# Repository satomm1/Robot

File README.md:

# Mobile Robot
This repository contains many instructions for setting up and constructing the robot. However, for a comprehensive guide, please visit: [https://satomm1.github.io/mattbot/instructions.html](https://satomm1.github.io/mattbot/index.html).

## Authors
Matthew Sato and Kincho Law<br>
satomm@stanford.edu<br>
Stanford University Department of Civil and Environmental Engineering<br>
Engineering Informatics Lab

## Description
This repo contains mechanical (CAD) designs, electrical schematics, and software for creating a wheeled mobile robot.

- The mechanical design is provided in the `./CAD` directory. In this directory, you will find [detailed instructions](./CAD/README.md) for constructing the mobile robot along with relevant STL/DXF files and a bill of materials. The CAD files were generated in Inventor.
- The electrical design for the various components are located in the `./Electrical` directory. In this directory, you will find electrical schematics and the PCB design for the main control board, IMU breakout board, microphone breakout board, and microphone controller board. A [detailed list of the components and instructions](./Electrical/README.md) for each of these boards is included.
- The software design for the main control board is in the `./Software` directory. This software is for the PIC32 located on the main control board and facilitates communication between the PIC32 and Jetson, performs PID control, odometry, etc. Additionally, the software for the microphone control board is included in this directory. Please visit the [README](./Software/README.md) for more detailed instructions.
- Instructions for the Nvidia Jetson Orin Nano aare provided in the `./Jetson` directory. This directory includes instructions for bringing up the Jetson, setting up the WiFi mesh node connectivity, setting up the Docker environments, and setting up the ROS environment/software stack. Please visit the [Jetson README](./Jetson/README.md) for more details.

## License

This project is licensed under the MIT License - see the [LICENSE](LICENSE) file for details.

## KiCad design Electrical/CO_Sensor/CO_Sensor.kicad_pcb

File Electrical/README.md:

# Electrical

Contains the electrical schematics and PCB gerber files for the Robot electronics. There are several Schematics/PCB designs for a variety of uses:
- Main Board - the main motor controller and communicator with the Jetson
- Microphone - a breakout board for a Mems omnidirectional microphone
- IMU Breakout - a breakout board containing a 6-axis IMU
- Reflective Sensor - a breakout board containing a sensor for very short distance measurements

The Main Board is the only required electronics, so start here. The others (IMU, reflective, microphone) provide additional functionality should you wish to include them.

## Ordering a Manufactured PCB Board
You can use a variety of vendors to order a PCB. I have used JLPCB in the past. To order, all you need to do is submit the zipped `gerber_files` folder to the vendor.

## Main Board
The [main board](./MainBoard/) contains the PIC32 MCU, motor drivers, power supply, button sensors, Jetson communications, etc. In this directory, you will find a comprehensive schematic and PCB layout, as well as ready to use Gerber files for PCB manufacturing.

After populating the board, we need to make several connections from the board to other components of the mobile robot:

1. Connecting to the motors

    - The motors should be connected to the motor terminals via a 6 position female molex connector. Insert the wires corresponding to the markings on the PCB silkscreen.

2. Connecting to the Jetson

    - The jetson is connected via a 6 position female molex connector on the PCB, and dupont connectors on the Jetson header. Only the first five positions on the PCB need to be connected (SCK, SS, SDO, SDI, GND) and must be matched to the corresponding SPI pins on the Jetson header. For example, if using SPI1 (SPI3) on the jetson:

        | Jetson Pin Name       | Jetson GPIO | PCB Pin Name |
        |-----------------------|-------------|--------------|
        | SPI1_SCLK (SPI3_SCLK) | 23 (13)     | SCK          |
        | SPI1_CS0 (SPI3_CS0)   | 24 (18)     | SS           |
        | SPI1_din (SPI3_din)   | 21 (22)     | SDO          |
        | SPI1_dout (SPI3_dout) | 19 (37)     | SDI          |
        | GND                   | 25 (20)     | GND          |

    - **Note:** If using twisted pair wire, **DO NOT** twist the SDO and SDI wires together. This will lead to unintended crosstalk that can significantly degrade the ability of the Jetson to communicate with the PCB.

3. Connecting to the power supply
    
    - Insert the Tamiya style leads for the NiMH batteries into the tall power blocks. The positive (red) and negative (black) terminals are indicated on the PCB via +/- silkscreen. 
    - Connect to the main power switch. The rocker switch should be connected to the 4 position Molex terminal near the battery terminals. Solder four wires to the rocker switch (with heat shrink tubing to protect the connection) and connect the other four ends to the corresponding female molex connector. The positions are as follows:

    - Insert a 5A fuse into the fuse holder.
    - Insert the micro-usb cable for the 5V battery into the port at the front of the board (the other micro-usb port is used for serial debugging)
    - Now, you can power on the PCB with the rocker switch. Alternatively, the small switch on the PCB is used to provide only 5V power supply access to the board in case you do not need to run the motors.

4. Connecting to the buttons
    
    - Solder a pair of wires to each button (with heat shrink tubing to protect the cunnection) and connect the other ends of the wire to a 2-position female molex connector.

## Microphone

For detailed instructions on the Microphone, visit the [Microphone README Page](./Microphones/README.md).

## IMU Breakout
For detailed instructions on the IMU, visit the [IMU README Page](./IMU_Breakout/README.md).

## Reflective Sensor

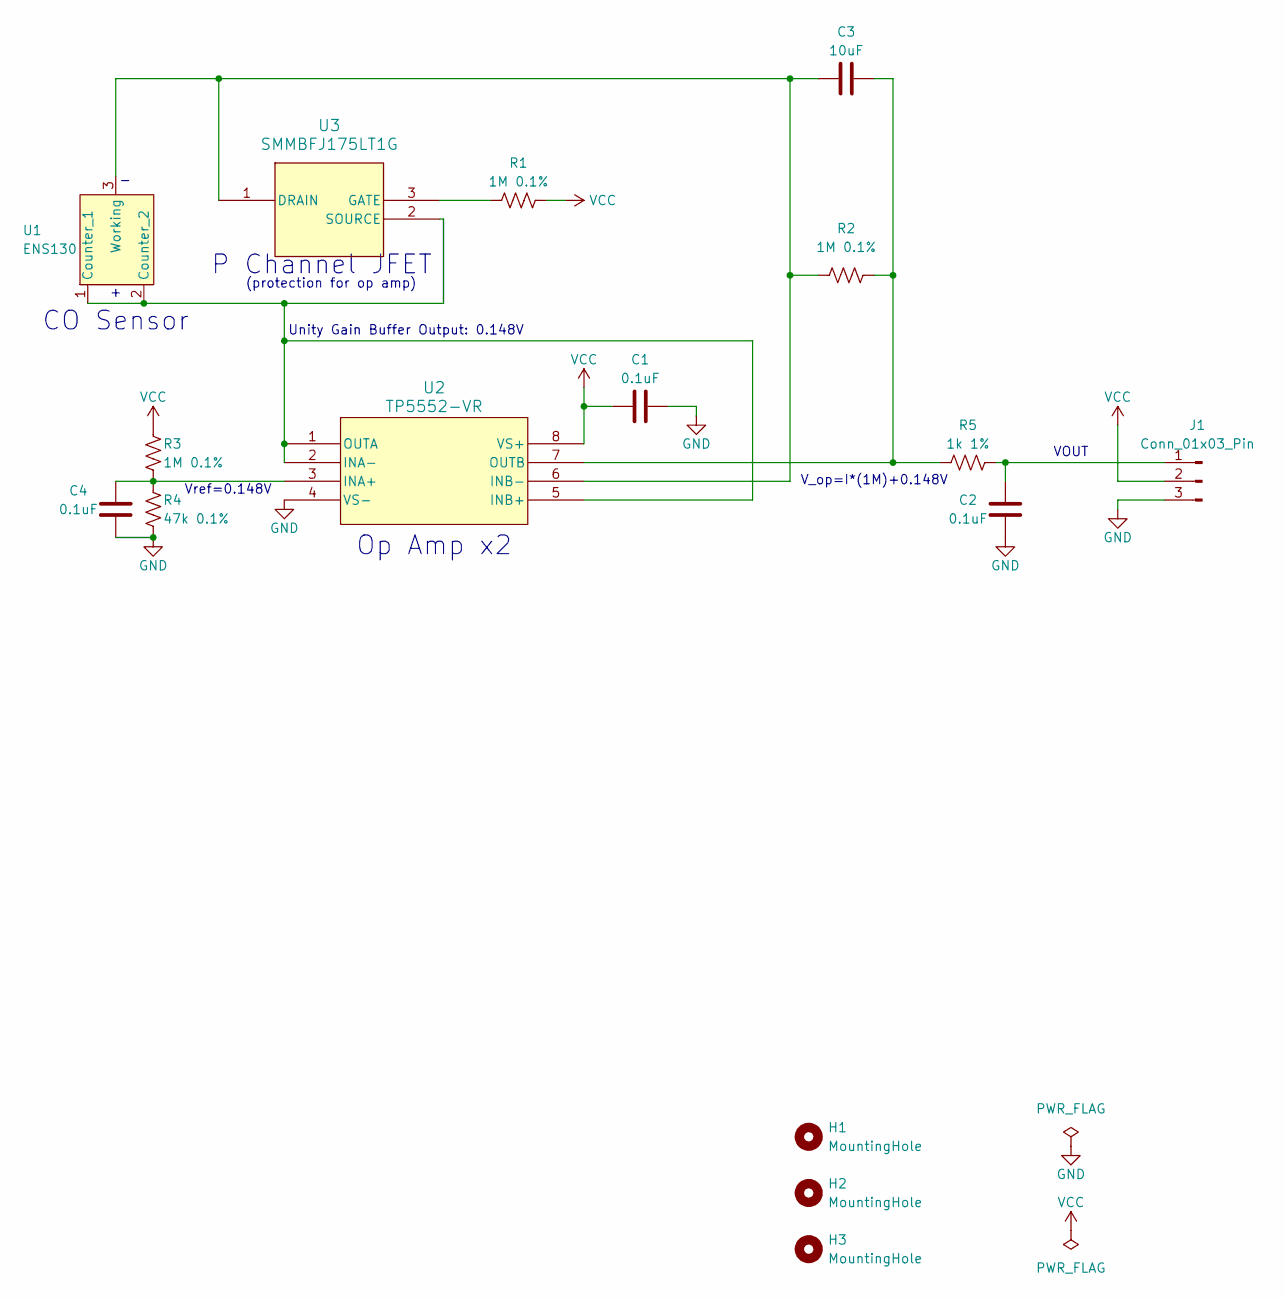
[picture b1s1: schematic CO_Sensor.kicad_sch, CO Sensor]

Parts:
C1, C2, C4: 0.1uF; C_0805_2012Metric_Pad1.18x1.45mm_HandSolder; Mfr P/N CL21B104KBCNNNC
C3: 10uF; C_0805_2012Metric_Pad1.18x1.45mm_HandSolder; Mfr P/N CL21A106KOQNNNE
H1, H2, H3: MountingHole; MountingHole_3.2mm_M3
J1: Conn_01x03_Pin; PinHeader_1x03_P2.54mm_Vertical
R1, R2, R3: 1M 0.1%; R_0805_2012Metric_Pad1.20x1.40mm_HandSolder; Mfr P/N ERA-6AEB105V
R4: 47k 0.1%; R_0805_2012Metric_Pad1.20x1.40mm_HandSolder; Mfr P/N ERA-6AEB473V
R5: 1k 1%; R_0805_2012Metric_Pad1.20x1.40mm_HandSolder; Mfr P/N RMCF0805FT1K00
U1: ENS130; Mfr P/N ENS130
U2: TP5552-VR; VS1MSOP-8-A_TPK-M; Mfr P/N TP5552-VR
U3: SMMBFJ175LT1G; SOT-23_ONS-M; Mfr P/N SMMBFJ175LT1G

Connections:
GND: C1.2, C2.1, C4.1, J1.3, R4.1, U2.4 (VS-)
unnamed: C2.2, J1.1, R5.1
unnamed: U1.1 (Counter_1), U1.2 (Counter_2), U2.1 (OUTA), U2.2 (INA-), U2.5 (INB+), U3.2 (SOURCE)
unnamed: C3.1, R2.1, U1.3 (Working), U2.6 (INB-), U3.1 (DRAIN)
unnamed: C4.2, R3.1, R4.2, U2.3 (INA+)
unnamed: C3.2, R2.2, R5.2, U2.7 (OUTB)
unnamed: R1.1, U3.3 (GATE)
VCC: C1.1, J1.2, R1.2, R3.2, U2.8 (VS+)

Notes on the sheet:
Unity Gain Buffer Output: 0.148V
CO Sensor
P Channel JFET
Op Amp x2
Vref=0.148V
(protection for op amp)
VOUT
V_op=I*(1M)+0.148V

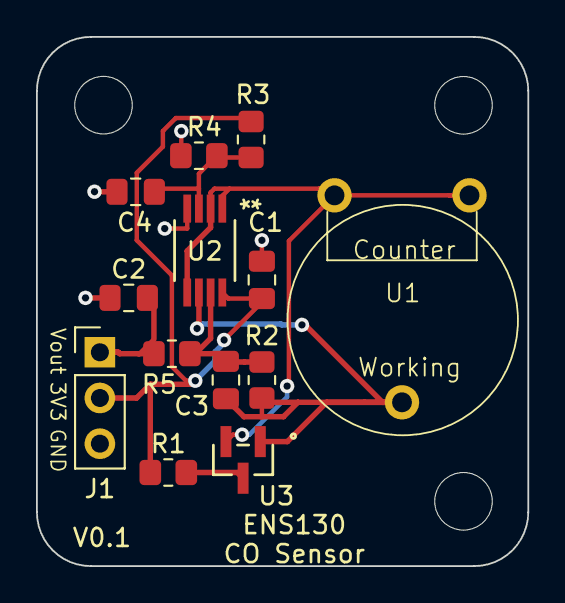
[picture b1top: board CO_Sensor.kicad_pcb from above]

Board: 2 copper layers, 27.3 x 29.4 mm, 16 parts (0 on the bottom side), 8 nets.

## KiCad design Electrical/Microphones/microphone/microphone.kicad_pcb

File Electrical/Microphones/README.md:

# Microphone Design

This directory holds the electrical design for the microphones. Note, you will need one  PIC32 board and two microphone boards for a single system. The two microphones allows for stereo audio. The PIC32 board is an intermediary that translates the audio signal into a format that the Jetson can read.

> [!WARNING] 
> Soldering the microphones is not easy. You will need solder paste and a reflow oven.  You can order a stencil for the solder paste, or manually apply the solder paste to the microphone pads (be careful not to add too much solder!).

> [!TIP]
> Make sure to solder the 6 pin right angle connector in the correct direction. See picture below for guidance.

## Putting the Microphones Together
Once you have a soldered microphone PCB, we can construct the full microphone in its housing. 3D print the housings (instructions in the [Mechanical Directory](../../CAD/README.md)). For a more robust microphone, we use a gasket and an acoustically transparent fabric to prevent debris from entering the microphone port. To construct the housing

1. Attach the gasket, making a hole slightly larger than the microphone port (be sure the hole is big enough even after the gasket is compressed). For the gasket, I use a foam-like double sided tape.

2. Place the acoustically transparent membrane over the gasket and PCB, cut holes for the screws. For the acoustically transparent fabric, I use Muslin (which can be picked up at your local fabric store).

3. Attach the PCB to the 3D printed housing using two screws.

4. Connect the two microphones to the PIC32 Control Board using Molex Connectors.

## Setting up the PIC32
Once you have a soldered PIC32, you must program it with the source code located in the [PIC32 Firmware](./PIC32%20Firmware/) directory. Connect the two microphones to the PIC32 board. Connect the PIC32 board to the Jetson's I2S pins. Then, follow the instructions at https://github.com/satomm1/mattbot_record/tree/noetic for Jetson software.

## PIC32 to Jetson I2S Pin Mapping

We will be using the 6-pin connector for this microphone (ignore the 5 pin header). Make sure the switch is switched in the upward position. Then, connect the pins on the PIC32 Board to the Jetson using the following connections (may need to adjust pin # based on your hardware):

| PIC32 Pin | Jetson I2S Pin | Jetson I2S Pin Number |
|-----------|----------------|-----------------------|
| CS        | I2S2_FS        | 35 |
| SDI       | I2S2_DOUT      | 40 |
| SDO       | I2S2_DIN       | 38 |
| SCK       | I2S2_SCLK      | 12 |
| GND       | GND            | 14 |
| 3V3       | 3.3V           | 17 |

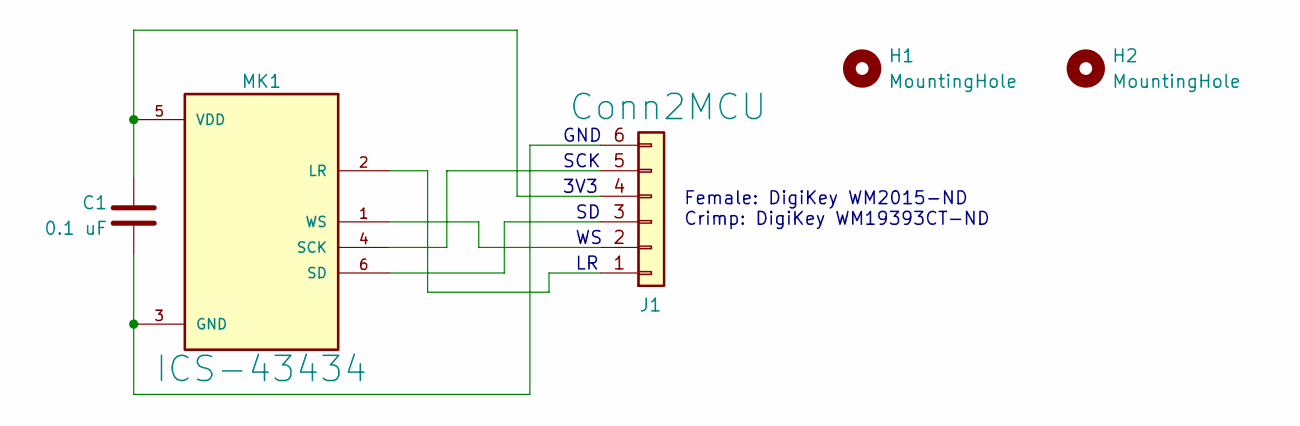
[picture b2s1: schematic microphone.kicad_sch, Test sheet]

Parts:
C1: 0.1 uF; C_0805_2012Metric_Pad1.18x1.45mm_HandSolder; Mfr P/N CL21B104KBCNNNC
H1, H2: MountingHole; MountingHole_3.2mm_M3
J1: Conn2MCU; CONN_22-05-3061_MOL; Mfr P/N 0022053061
MK1: ICS-43434; MIC_ICS-43434; Mfr P/N ICS-43434

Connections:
unnamed: J1.1, MK1.2 (LR)
unnamed: J1.2, MK1.1 (WS)
unnamed: J1.3, MK1.6 (SD)
unnamed: C1.1, J1.4, MK1.5 (VDD)
unnamed: J1.5, MK1.4 (SCK)
unnamed: C1.2, J1.6, MK1.3 (GND)

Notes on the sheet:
GND
Female: DigiKey WM2015-ND Crimp: DigiKey WM19393CT-ND
3V3
SCK

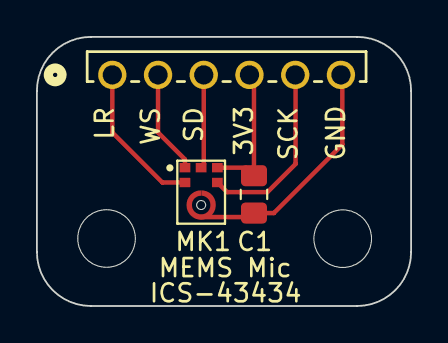
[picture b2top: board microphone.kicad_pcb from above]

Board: 2 copper layers, 20.8 x 15.0 mm, 5 parts (0 on the bottom side), 6 nets.

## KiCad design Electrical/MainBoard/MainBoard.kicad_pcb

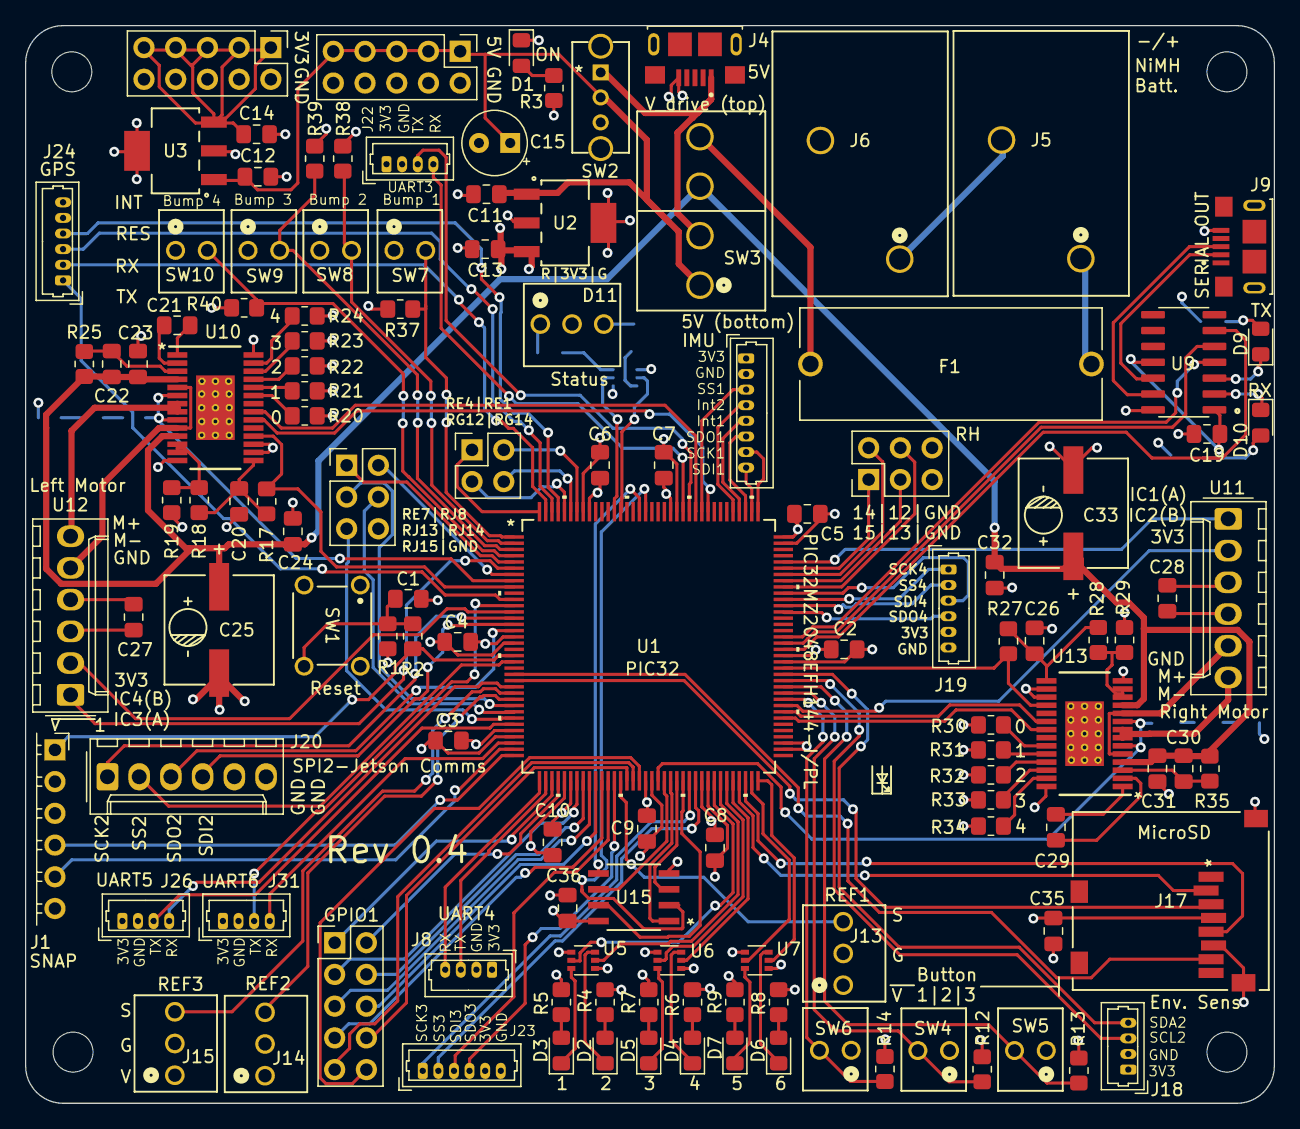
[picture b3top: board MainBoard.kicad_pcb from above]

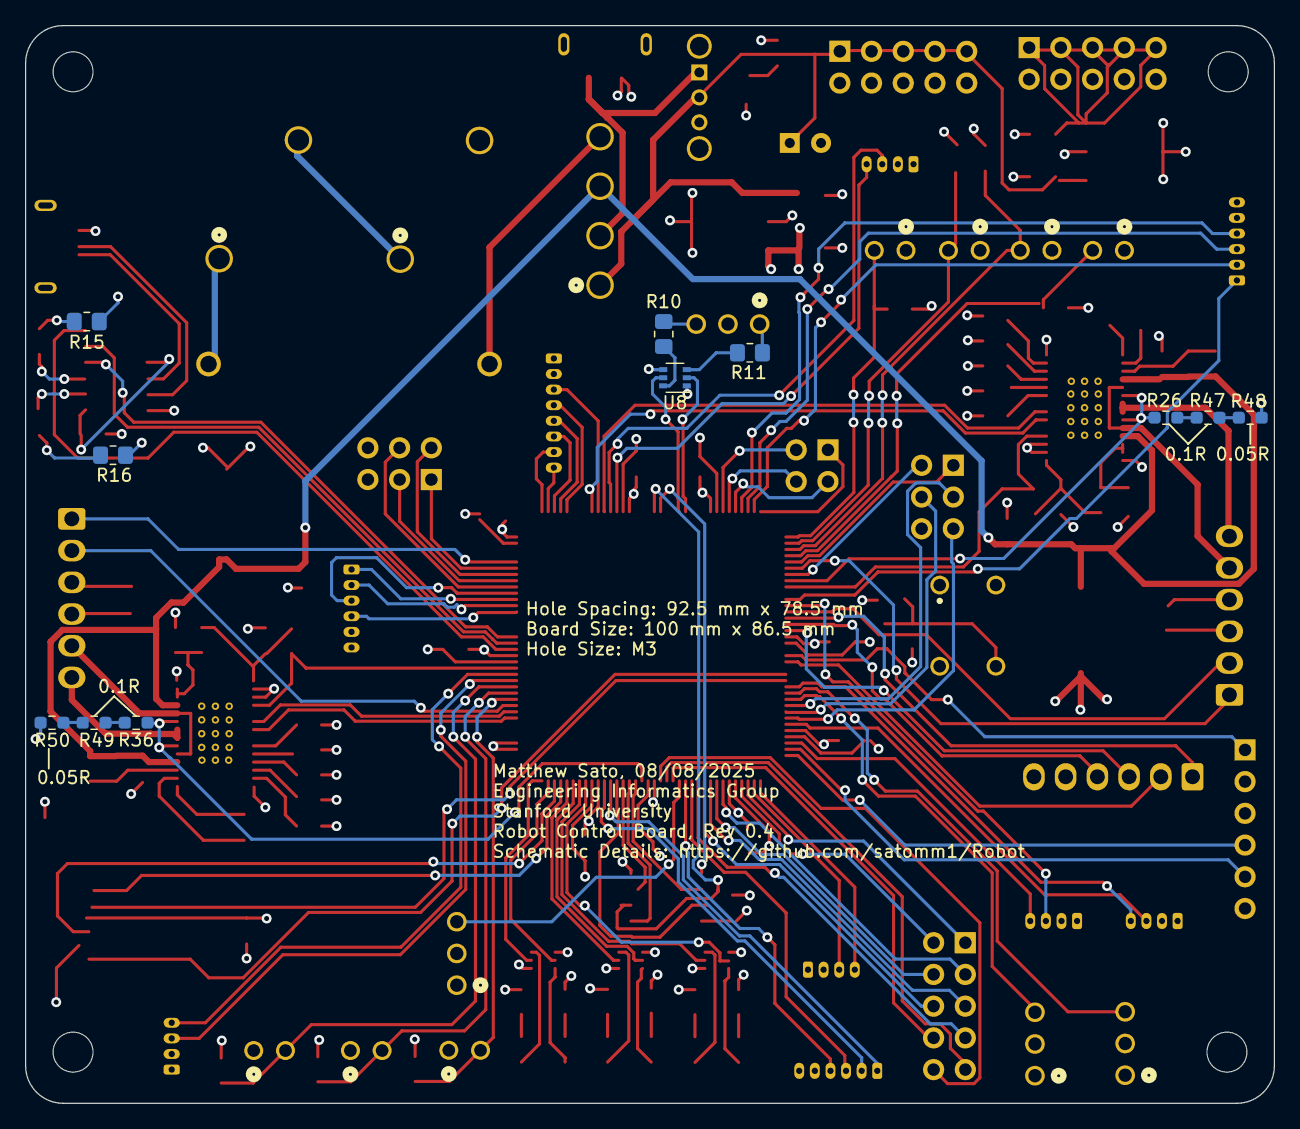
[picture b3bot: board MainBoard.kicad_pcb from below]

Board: 4 copper layers, 100.0 x 86.3 mm, 139 parts (11 on the bottom side), 162 nets.

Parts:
C1, C2, C3, C4, C5, C6, C7, C8, C9, C10, C19, C22, C23, C24, C27, C28, C30, C31, C32, C35, C36: 0.1 uF; C_0805_2012Metric_Pad1.18x1.45mm_HandSolder
C11, C12, C13, C14: 4.7 uF; C_0805_2012Metric_Pad1.18x1.45mm_HandSolder
C15: 10 uF; CP_Radial_Tantal_D5.0mm_P2.50mm
C20, C26: 0.47 uF; C_0805_2012Metric_Pad1.18x1.45mm_HandSolder
C21, C29: 0.01 uF; C_0805_2012Metric_Pad1.18x1.45mm_HandSolder
C25, C33: 100 uF; PCAP_8x10-ELECT_NCA-M
D1, D2, D3, D4, D5, D6, D7, D9, D10: LED; LED_0805_2012Metric_Pad1.15x1.40mm_HandSolder
D11: Status_LED; CONN3_22232031_MOL
F1: 5A Fuse; FUSE_4628
H1, H2, H3, H4: MountingHole; MountingHole_3.2mm_M3
J1: SNAP Program; PinSocket_1x06_P2.54mm_Horizontal
J2: 3.3V Supply; PinHeader_2x05_P2.54mm_Vertical
J3: 5V Supply; PinHeader_2x05_P2.54mm_Vertical
J4, J9: USB_B_Micro; AMPHENOL_10118193-0001LF
J5, J6: Battery1; CONN_1017514
J7: GPIO1; PinHeader_2x05_P2.54mm_Vertical
J8, J18, J22, J26, J31: Conn_01x04; Molex_PicoBlade_53047-0410_1x04_P1.25mm_Vertical
J13, J14, J15: Refl_PCB_Connect; CONN3_22232031_MOL
J16, J21: Conn_02x03_Odd_Even; PinHeader_2x03_P2.54mm_Vertical
J17: MEM2061-01-188-00-A; MEM2061-01-188-00-A_GCT
J19, J23, J24: Conn_01x06; Molex_PicoBlade_53047-0610_1x06_P1.25mm_Vertical
J20: Conn_01x06; Molex_KK-254_AE-6410-06A_1x06_P2.54mm_Vertical
J25: Conn_02x02_Odd_Even; PinHeader_2x02_P2.54mm_Vertical
J30: Conn_01x08; Molex_PicoBlade_53047-0810_1x08_P1.25mm_Vertical
R1, R17, R27: 10k; R_0805_2012Metric_Pad1.20x1.40mm_HandSolder
R2, R12, R13, R14, R37, R38, R39, R40: 1k; R_0805_2012Metric_Pad1.20x1.40mm_HandSolder
R3, R4, R5, R6, R7, R8, R9, R10, R11, R15, R16: 130R; R_0805_2012Metric_Pad1.20x1.40mm_HandSolder
R18, R28: 16k; R_0805_2012Metric_Pad1.20x1.40mm_HandSolder
R19, R29: 51k; R_0805_2012Metric_Pad1.20x1.40mm_HandSolder
R20, R21, R22, R23, R24, R30, R31, R32, R33, R34: 0R; R_0805_2012Metric_Pad1.20x1.40mm_HandSolder
R25, R35: 1M; R_0805_2012Metric_Pad1.20x1.40mm_HandSolder
R26, R36, R47, R49: 0.1R; R_0603_1608Metric_Pad0.98x0.95mm_HandSolder
R48, R50: 0.05 R; R_0603_1608Metric_Pad0.98x0.95mm_HandSolder
SW1: Reset; SW_B3F-1000_OMR
SW2: 5V Bypass; SPDT_OS102011_CNK
SW3: All Power Switch; 26-60-4040_MOL
SW4, SW5, SW6: User_Button; CONN_22232021_MOL
SW7, SW8, SW9, SW10: SW_SPST; CONN_22232021_MOL
U1: PIC32MZ2048EFH144-I/PL; LQFP144_PL_MCH-M
U2, U3: AP2114HA-3.3TRG1; SOT-223_DIO-M
U5, U6, U7, U8: GSF7002DW; SOT-363_SC-70-6
U9: MCP2221A-I_SL; SOIC127P600X175-14N
U10, U13: DRV8842PWPR; PWP0028C_M
U11, U12: Quad_Encoder_Motor; Molex_KK-254_AE-6410-06A_1x06_P2.54mm_Vertical
U15: M95M01-DFMN6TP; SO8N_4X5X1P27_STM-M

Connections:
+3.3V: C2.1, C3.2, C4.2, C5.1, C6.1, C7.2, C8.1, C9.1, C10.2, C13.1, C19.1, C27.1, C28.1, C35.2, C36.2, D11.2 (A), J1.2, J8.1, J13.1, J14.1, J15.1, J17.P4 (VDD), J18.1, J19.5, J22.1, J23.5, J24.5, J26.1, J30.1, J31.1, R1.2, R3.1, R4.1, R5.1, R6.1, R7.1, R8.1, R9.1, R15.1, R16.1, R20.1, R21.1, R22.1, R23.1, R24.1, R30.1, R31.1, R32.1, R33.1, R34.1, SW4.1, SW5.1, SW6.1, SW7.1 (A), SW8.1 (A), SW9.1 (A), SW10.1 (A), U1.18 (VDD), U1.33 (VDD), U1.41 (AVDD), U1.55 (VDD), U1.64 (VDD), U1.88 (VDD), U1.107 (VDD), U1.122 (VDD), U1.137 (VDD), U2.3 (VOUT), U9.1 (VDD), U9.11 (VUSB), U10.16 (RESET_N), U10.17 (SLEEP_N), U11.3 (Vcc), U12.3 (Vcc), U13.16 (RESET_N), U13.17 (SLEEP_N), U15.8 (VCC)
+5V: C11.1, C12.1, C15.1, J3.1, J3.3, J3.5, J3.7, J3.9, SW2.2 (B), SW3.1, U2.1 (VIN), U3.1 (VIN)
/Bump1: R37.1, SW7.2 (B), U1.1 (AN23/RG15)
/Bump2: R38.1, SW8.2 (B), U1.2 (EBIA5/AN34/PMA5/RA5)
/Bump3: R39.1, SW9.2 (B), U1.3 (EBID5/AN17/RPE5/PMD5/RE5)
/Bump4: R40.1, SW10.2 (B), U1.4 (EBID6/AN16/PMD6/RE6)
/Dir1: U1.80 (SCL3/RPF8/RF8), U13.20 (IN2)
/Dir2: U1.117 (EBIA22/RJ3), U10.20 (IN2)
/Fault1: R17.1, U1.9 (EBIBS0/RJ12), U10.18 (FAULT_N)
/Fault2: R27.1, U1.87 (EBIA14/PMCS1/PMA14/RA4), U13.18 (FAULT_N)
/GPS_INT: J24.4, U1.141 (TRD0/SQID0/RG13)
/GPS_Reset: J24.3, U1.142 (EBID2/PMD2/RE2)
/Hold*: U1.60 (AN8/RB13), U15.7 (*HOLD)
/IC1: U1.104 (RPD0/RTCC/INT0/RD0), U11.1 (PhaseA)
/IC2: U1.81 (ERXD0/RH8), U11.2 (PhaseB)
/IC3: U1.6 (EBIA6/AN22/RPC1/PMA6/RC1), U12.1 (PhaseA)
/IC4: U1.13 (EBIOE/AN19/RPC4/PMRD/RC4), U12.2 (PhaseB)
/IMU_INT1: J30.5, U1.112 (EBID12/RPD12/PMD12/RD12)
/IMU_INT2: J30.4, U1.113 (EBID13/PMD13/RD13)
/LED1: U1.66 (AN41/ERXD1/RH5), U5.2 (G1)
/LED2: U1.65 (AN40/ERXERR/RH4), U5.5 (G2)
/LED3: U1.68 (EBIA4/PMA4/RH7), U6.2 (G1)
/LED4: U1.67 (AN42/ERXD2/RH6), U6.5 (G2)
/LED5: U1.72 (OSC2/CLKO/RC15), U7.2 (G1)
/LED6: U1.71 (OSC1/CLKI/RC12), U7.5 (G2)
/MotorCurrent1: R26.2, U1.8 (AN36/ETXD1/RJ9), U10.6 (ISEN), U10.9 (ISEN)
/MotorCurrent2: R36.2, U1.56 (TCK/AN29/RA1), U13.6 (ISEN), U13.9 (ISEN)
/OC1: U1.79 (SDA3/RPF2/RF2), U13.21 (IN1)
/OC2: U1.119 (SQICS1/RPD5/RD5), U10.21 (IN1)
/RA9: J7.1, U1.39 (VREF-/CVREF-/AN27/RA9)
/RA10: J7.2, U1.40 (VREF+/CVREF+/AN28/RA10)
/RB8: J7.7, U1.47 (EBIA10/AN48/RPB8/PMA10/RB8)
/RE1: J25.2, U1.138 (EBID1/PMD1/RE1)
/RE4: J25.1, U1.144 (EBID4/AN18/PMD4/RE4)
/RE7: J16.1, U1.5 (EBID7/AN15/PMD7/RE7)
/RG12: J25.3, U1.140 (TRD1/SQID1/RG12)
/RG14: J25.4, U1.139 (TRD2/SQID2/RG14)
/RH0: J7.3, U1.43 (AN38/ETXD2/RH0)
/RH1: J7.4, U1.44 (AN39/ETXD3/RH1)
/RH2: J7.5, U1.45 (EBIRP/RH2)
/RH3: J7.6, U1.46 (RH3)
/RH12: J21.4, U1.100 (ECRS/RH12)
/RH13: J21.3, U1.101 (ERXDV/ECRSDV/RH13)
/RH14: J21.2, U1.102 (RH14)
/RH15: J21.1, U1.103 (EBIA23/RH15)
/RJ8: J16.2, U1.7 (AN35/ETXD0/RJ8)
/RJ13: J16.3, U1.28 (EBIA13/PMA13/RJ13)
/RJ14: J16.4, U1.29 (EBIA11/PMA11/RJ14)
/RJ15: J16.5, U1.30 (EBIA0/PMA0/RJ15)
/RK1: J7.8, U1.51 (EBIA1/PMA1/RK1)
/RK2: J7.9, U1.52 (EBIA3/PMA3/RK2)
/RK3: J7.10, U1.53 (EBIA17/RK3)
/Refl1: J13.3, U1.50 (AN6/RB11)
/Refl2: J14.3, U1.27 (AN37/ERXCLK/EREFCLK/RJ11)
/Refl3: J15.3, U1.26 (AN4/C1INB/RB4)
/SCK1: J30.7, U1.109 (RPD1/SCK1/RD1)
/SCK2: J20.1, U1.14 (AN14/C1IND/RPG6/SCK2/RG6)
/SCK3: J23.1, U1.61 (AN9/RPB14/SCK3/RB14)
/SCK4: J19.1, U1.98 (RPD10/SCK4/RD10)
/SCK5: U1.57 (TDI/AN30/RPF13/SCK5/RF13), U15.6 (C)
/SCK6: J17.P5 (CLK), U1.70 (AN33/RPD15/SCK6/RD15)
/SCL2: J18.3, U1.85 (SCL2/RA2)
/SDA2: J18.4, U1.86 (EBIRDY1/SDA2/RA3)
/SDI1: J30.8, U1.110 (EBID14/RPD2/PMD14/RD2)
/SDI2: J20.4, U1.15 (AN13/C1INC/RPG7/SDA4/RG7)
/SDI3: J23.3, U1.48 (EBIA7/AN49/RPB9/PMA7/RB9)
/SDI4: J19.3, U1.99 (EMDC/RPD11/RD11)
/SDI5: U1.127 (EBID9/RPG1/PMD9/RG1), U15.2 (Q)
/SDI6: J17.P7 (DAT0), U1.23 (AN25/RPE8/RE8)
/SDO1: J30.6, U1.111 (EBID15/RPD3/PMD15/RD3)
/SDO2: J20.3, U1.16 (AN12/C2IND/RPG8/SCL4/RG8)
/SDO3: J23.4, U1.49 (CVREFOUT/AN5/RPB10/RB10)
/SDO4: J19.4, U1.96 (RPA15/SDA1/RA15)
/SDO5: U1.128 (EBID8/RPG0/PMD8/RG0), U15.5 (D)
/SDO6: J17.P3 (CMD), U1.24 (AN26/RPE9/RE9)
/SS1*: J30.3, U1.118 (SQICS0/RPD4/RD4)
/SS2*: J20.2, U1.21 (EBIA2/AN11/C2INC/RPG9/PMA2/RG9)
/SS3*: J23.2, U1.62 (AN10/RPB15/OCFB/RB15)
/SS4*: J19.2, U1.97 (EBIA15/RPD9/PMCS2/PMA15/RD9)
/SS5*: U1.58 (TDO/AN31/RPF12/RF12), U15.1 (*S)
/SS6*: J17.P2 (CD/DAT3), U1.69 (AN32/RPD14/RD14)
/Status_Green: U1.132 (EBICS1/RJ5), U8.2 (G1)
/Status_Yellow: U1.131 (EBICS0/RJ4), U8.5 (G2)
/Switch1: R14.1, SW6.2, U1.82 (ERXD3/RH9)
/Switch2: R12.1, SW4.2, U1.83 (ECOL/RH10)
/Switch3: R13.1, SW5.2, U1.84 (EBIRDY2/RH11)
/U1RX: U1.90 (EBIA9/RPF4/SDA5/PMA9/RF4), U9.6 (UTX)
/U1TX: U1.91 (EBIA8/RPF5/SCL5/PMA8/RF5), U9.5 (URX)
/U2RX: J24.2, U1.143 (EBID3/RPE3/PMD3/RE3)
/U2TX: J24.1, U1.11 (EBIA12/AN21/RPC2/PMA12/RC2)
/U3RX: J22.4, U1.121 (ETXCLK/RPD7/RD7)
/U3TX: J22.3, U1.120 (ETXEN/RPD6/RD6)
/U4RX: J8.4, U1.37 (PGEC2/AN46/RPB6/RB6)
/U4TX: J8.3, U1.38 (PGED2/AN47/RPB7/RB7)
/U5RX: J26.4, U1.25 (AN45/C1INA/RPB5/RB5)
/U5TX: J26.3, U1.31 (AN3/C2INA/RPB3/RB3)
/U6RX: J31.4, U1.34 (AN2/C2INB/RPB2/RB2)
/U6TX: J31.3, U1.12 (EBIWE/AN20/RPC3/PMWR/RC3)
/USB_RST: U1.92 (EBIA18/RK4), U9.4 (~RST)
/Write Protect*: U1.59 (AN7/RB12), U15.3 (*W)
GND: C1.2, C2.2, C3.1, C4.1, C5.2, C6.2, C7.1, C8.2, C9.2, C10.1, C11.2, C12.2, C13.2, C14.2, C15.2, C19.2, C20.2, C23.2, C24.2, C25.2, C26.2, C27.2, C28.2, C31.2, C32.2, C33.2, C35.1, C36.1, D1.1 (K), J1.3, J2.2, J2.4, J2.6, J2.8, J2.10, J3.2, J3.4, J3.6, J3.8, J3.10, J4.5 (GND), J6.2, J8.2, J9.5 (GND), J13.2, J14.2, J15.2, J16.6, J17.11 (GROUND), J17.12 (GROUND), J17.P6 (VSS), J18.2, J19.6, J20.5, J20.6, J21.5, J21.6, J22.2, J23.6, J24.6, J26.2, J30.2, J31.2, R12.2, R13.2, R14.2, R19.2, R29.2, R37.2, R38.2, R39.2, R40.2, R48.1, R50.1, SW1.1, U1.17 (VSS), U1.32 (VSS), U1.42 (AVSS), U1.54 (VSS), U1.63 (VSS), U1.74 (VUSB3V3), U1.75 (VSS), U1.89 (VSS), U1.108 (VSS), U1.123 (VSS), U1.136 (VSS), U2.2 (GND), U2.4 (GND), U3.2 (GND), U3.4 (GND), U5.1 (S1), U5.4 (S2), U6.1 (S1), U6.4 (S2), U7.1 (S1), U7.4 (S2), U8.1 (S1), U8.4 (S2), U9.14 (VSS), U10.14 (GND), U10.28 (GND), U10.29 (PAD), U11.4 (GND), U12.4 (GND), U13.14 (GND), U13.28 (GND), U13.29 (PAD), U15.4 (VSS)
unnamed: C1.1, R1.1, R2.2, SW1.4
unnamed: D1.2 (A), R3.2
unnamed: D2.2 (A), R4.2
unnamed: D2.1 (K), U5.3 (D2)
unnamed: D3.2 (A), R5.2
unnamed: D3.1 (K), U5.6 (D1)
unnamed: D4.2 (A), R6.2
unnamed: D4.1 (K), U6.3 (D2)
unnamed: D5.2 (A), R7.2
unnamed: D5.1 (K), U6.6 (D1)
unnamed: D6.2 (A), R8.2
unnamed: D6.1 (K), U7.3 (D2)
unnamed: D7.2 (A), R9.2
unnamed: D7.1 (K), U7.6 (D1)
unnamed: D9.2 (A), R15.2
unnamed: D9.1 (K), U9.3 (GP1)
unnamed: D10.2 (A), R16.2
unnamed: D10.1 (K), U9.2 (GP0)
unnamed: D11.1 (K1), R11.2
unnamed: D11.3 (K2), R10.2
unnamed: F1.1, SW3.4
unnamed: J1.1, R2.1, U1.20 (MCLR)
unnamed: J1.4, U1.36 (PGED1/AN0/RPB0/RB0)
unnamed: J1.5, U1.35 (PGEC1/AN1/RPB1/RB1)
unnamed: C14.1, J2.1, J2.3, J2.5, J2.7, J2.9, U3.3 (VOUT)
unnamed: J4.1 (VBUS), SW2.1 (A), SW3.2
unnamed: F1.2, J5.1
unnamed: J5.2, J6.1
unnamed: J9.3 (D+), U9.13 (D+)
unnamed: J9.2 (D-), U9.12 (D-)
unnamed: R18.2, R19.1, U10.12 (VREF), U10.13 (VREF)
unnamed: R26.1, R47.2
unnamed: R28.2, R29.1, U13.12 (VREF), U13.13 (VREF)
unnamed: R36.1, R49.2
unnamed: R47.1, R48.2
unnamed: R49.1, R50.2
unnamed: R10.1, U8.6 (D1)
unnamed: R11.1, U8.3 (D2)
unnamed: C21.1, U10.1 (CP1)
unnamed: C21.2, U10.2 (CP2)
unnamed: R20.2, U10.23 (I0)
unnamed: R21.2, U10.24 (I1)
unnamed: R22.2, U10.25 (I2)
unnamed: R23.2, U10.26 (I3)
unnamed: R24.2, U10.27 (I4)
unnamed: C20.1, R17.2, R18.1, U10.15 (V3P3OUT)
unnamed: C22.2, R25.2, U10.3 (VCP)
unnamed: U11.5 (M+), U13.5 (OUT1), U13.10 (OUT1)
unnamed: U11.6 (M-), U13.7 (OUT2), U13.8 (OUT2)
unnamed: U10.5 (OUT1), U10.10 (OUT1), U12.5 (M+)
unnamed: U10.7 (OUT2), U10.8 (OUT2), U12.6 (M-)
unnamed: C29.1, U13.1 (CP1)
unnamed: C29.2, U13.2 (CP2)
unnamed: R30.2, U13.23 (I0)
unnamed: R31.2, U13.24 (I1)
unnamed: R32.2, U13.25 (I2)
unnamed: R33.2, U13.26 (I3)
unnamed: R34.2, U13.27 (I4)
unnamed: C26.1, R27.2, R28.1, U13.15 (V3P3OUT)
unnamed: C30.1, R35.2, U13.3 (VCP)
Vdrive: C22.1, C23.1, C24.1, C25.1, C30.2, C31.1, C32.1, C33.1, R25.1, R35.1, SW3.3, U10.4 (VM), U10.11 (VM), U13.4 (VM), U13.11 (VM)

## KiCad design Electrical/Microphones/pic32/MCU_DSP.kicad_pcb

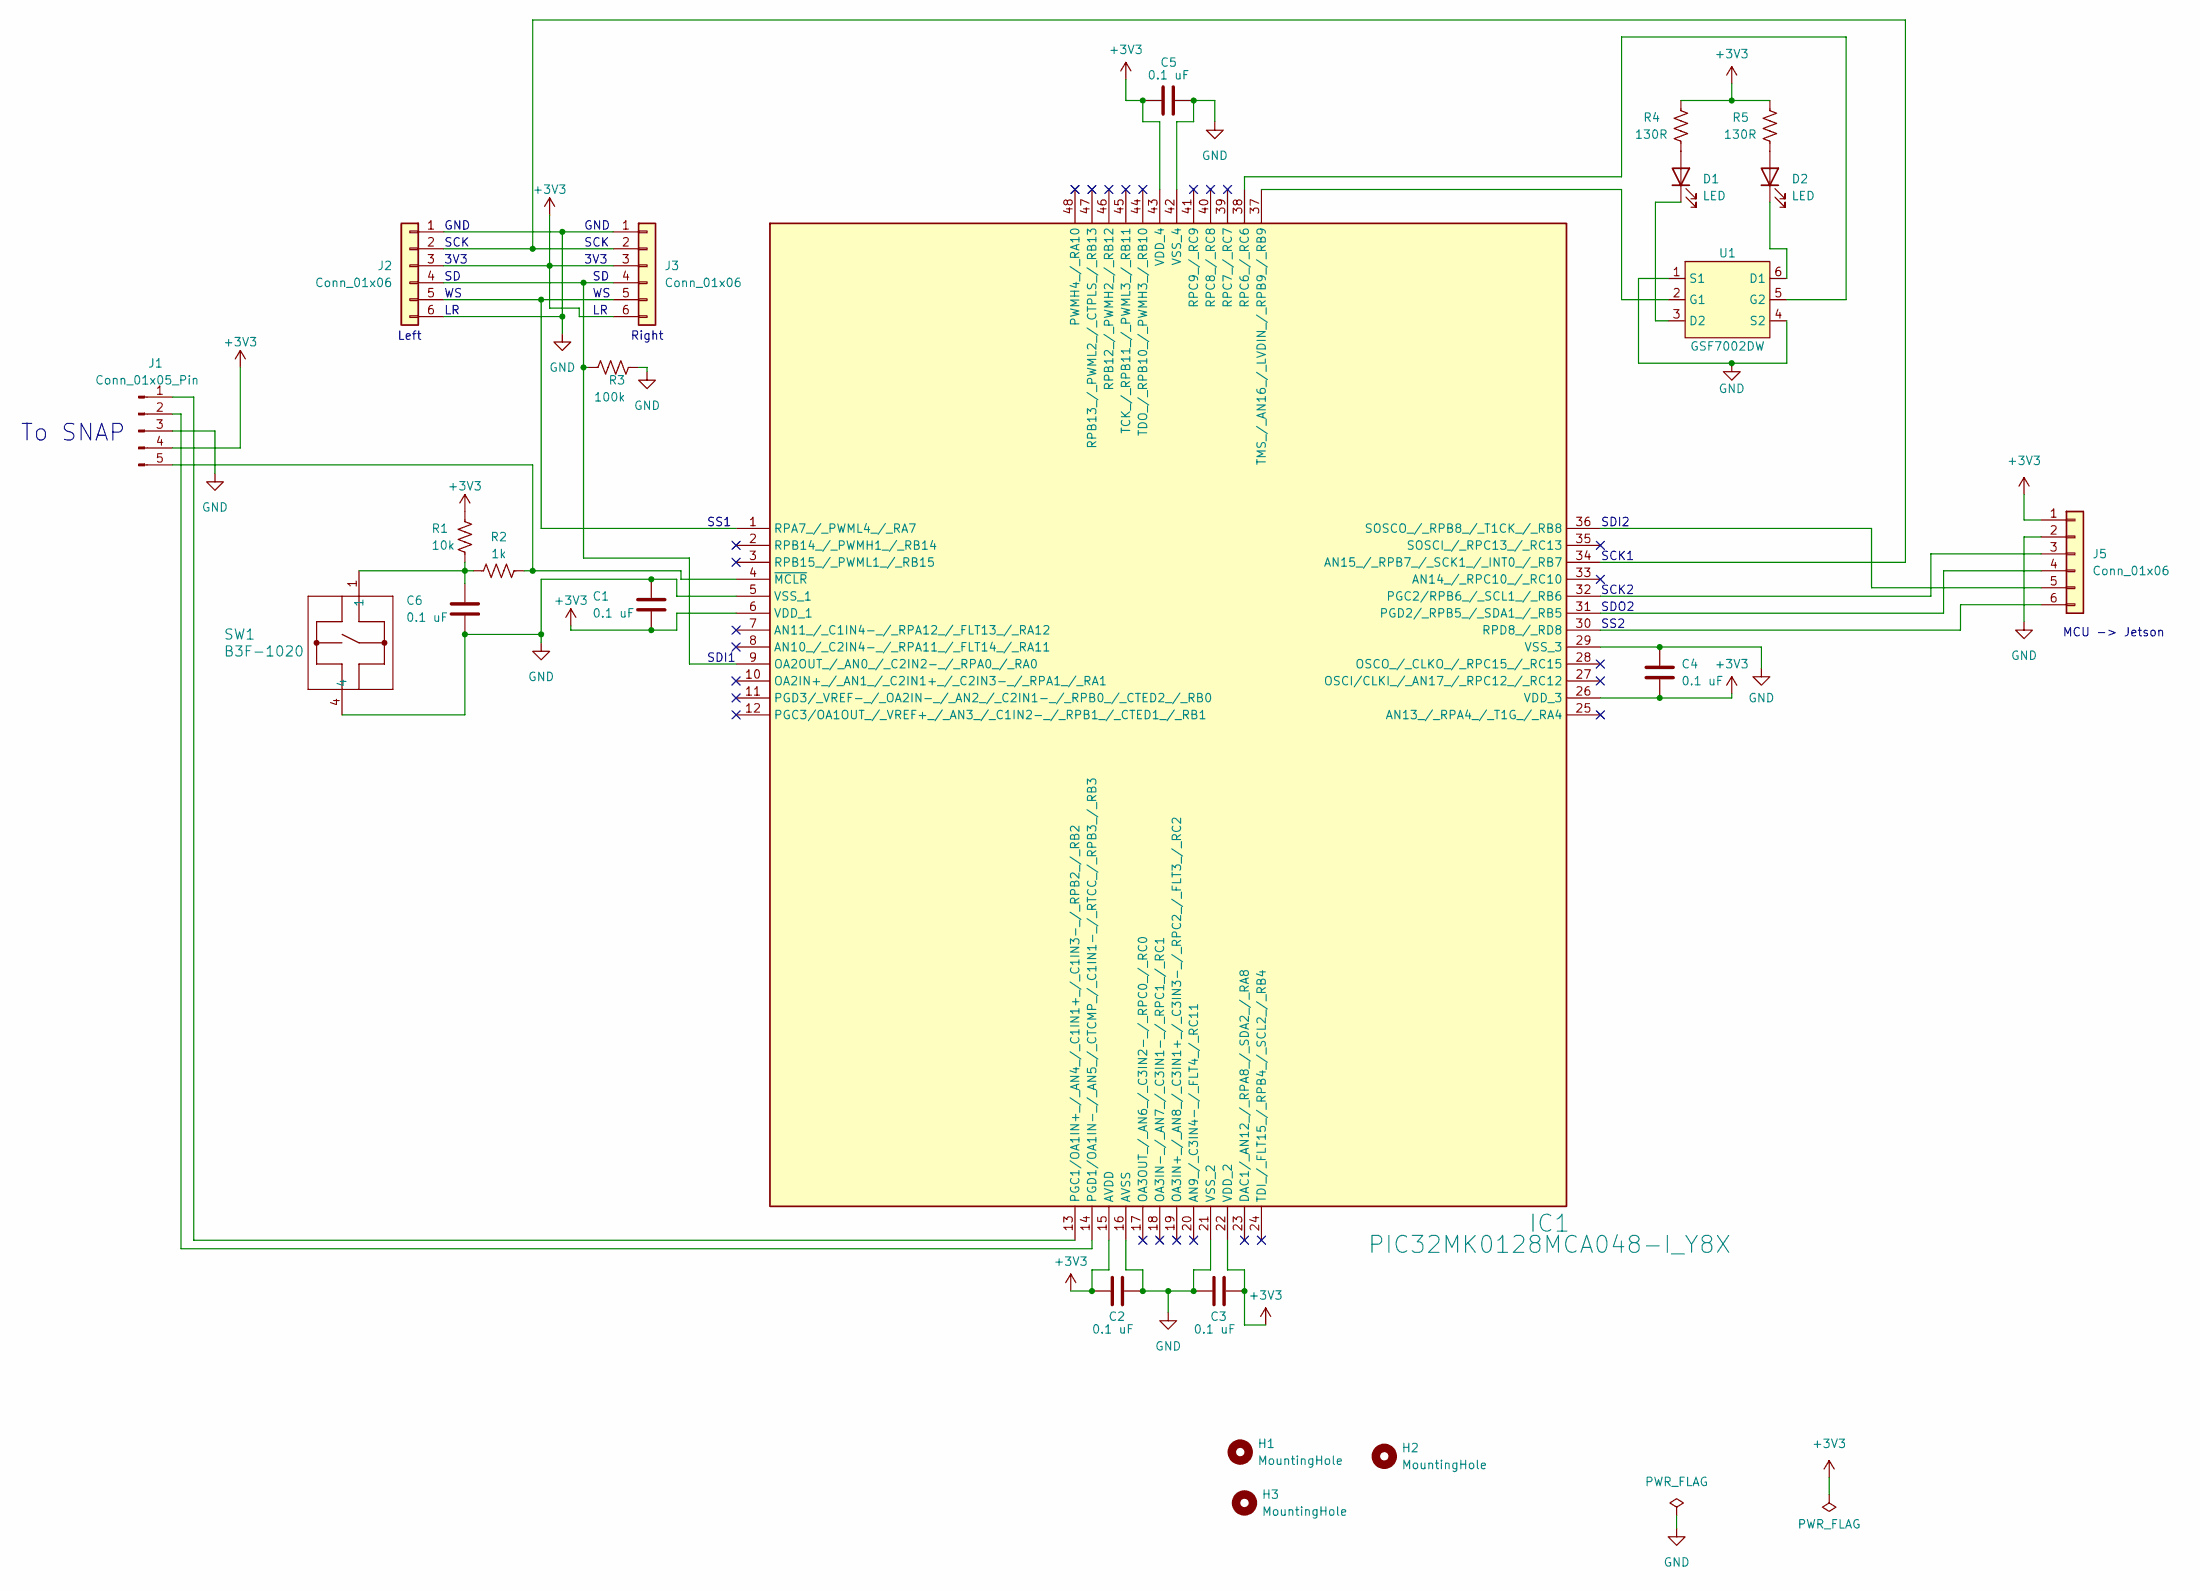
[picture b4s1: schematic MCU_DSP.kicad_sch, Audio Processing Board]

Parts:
C1, C2, C3, C4, C5, C6: 0.1 uF; C_0805_2012Metric_Pad1.18x1.45mm_HandSolder; Mfr P/N CL21B104KBCNNNC
D1, D2: LED; LED_0805_2012Metric_Pad1.15x1.40mm_HandSolder; Mfr P/N B1701URO-20D000114U1930
H1, H2, H3: MountingHole; MountingHole_3.2mm_M3
IC1: PIC32MK0128MCA048-I_Y8X; TQFP48_Y8X_MCH-M; Mfr P/N PIC32MK0128MCA048T-I/Y8X
J1: Conn_01x05_Pin; PinHeader_1x05_P2.54mm_Horizontal; Mfr P/N 10129379-910002BLF
J2, J3, J5: Conn_01x06; Molex_KK-254_AE-6410-06A_1x06_P2.54mm_Vertical; Mfr P/N 0022232061
R1: 10k; R_0805_2012Metric_Pad1.20x1.40mm_HandSolder; Mfr P/N RMCF0805JT10K0
R2: 1k; R_0805_2012Metric_Pad1.20x1.40mm_HandSolder; Mfr P/N RMCF0805FT1K00
R3: 100k; R_0805_2012Metric_Pad1.20x1.40mm_HandSolder; Mfr P/N RMCF0805FG100K
R4, R5: 130R; R_0805_2012Metric_Pad1.20x1.40mm_HandSolder; Mfr P/N RMCF0805FT130R
SW1: B3F-1020; SW_B3F-1000_OMR; Mfr P/N B3F-1020
U1: GSF7002DW; SOT-363_SC-70-6; Mfr P/N GSF7002DW

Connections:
+3V3: C1.2, C2.1, C3.2, C4.2, C5.2, IC1.6 (VDD_1), IC1.15 (AVDD), IC1.22 (VDD_2), IC1.26 (VDD_3), IC1.43 (VDD_4), J1.4, J2.3, J3.3, J3.6, J5.1, R1.1, R4.1, R5.1
GND: C1.1, C2.2, C3.1, C4.1, C5.1, C6.2, IC1.5 (VSS_1), IC1.16 (AVSS), IC1.21 (VSS_2), IC1.29 (VSS_3), IC1.42 (VSS_4), J1.3, J2.1, J2.6, J3.1, J5.2, R3.2, SW1.4, U1.1 (S1), U1.4 (S2)
unnamed: C6.1, R1.2, R2.1, SW1.1
unnamed: D1.2 (A), R4.2
unnamed: D1.1 (K), U1.3 (D2)
unnamed: D2.2 (A), R5.2
unnamed: D2.1 (K), U1.6 (D1)
unnamed: IC1.34 (AN15_/_RPB7_/_SCK1_/_INT0_/_RB7), J2.2, J3.2
unnamed: IC1.9 (OA2OUT_/_AN0_/_C2IN2-_/_RPA0_/_RA0), J2.4, J3.4, R3.1
unnamed: IC1.13 (PGC1/OA1IN+_/_AN4_/_C1IN1+_/_C1IN3-_/_R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), J1.1
unnamed: IC1.32 (PGC2/RPB6_/_SCL1_/_RB6), J5.3
unnamed: IC1.14 (PGD1/OA1IN-_/_AN5_/_CTCMP_/_C1IN1-_/_RT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), J1.2
unnamed: IC1.31 (PGD2/_RPB5_/_SDA1_/_RB5), J5.4
unnamed: IC1.1 (RPA7_/_PWML4_/_RA7), J2.5, J3.5
unnamed: IC1.38 (RPC6_/_RC6), U1.5 (G2)
unnamed: IC1.30 (RPD8_/_RD8), J5.6
unnamed: IC1.36 (SOSCO_/_RPB8_/_T1CK_/_RB8), J5.5
unnamed: IC1.37 (TMS_/_AN16_/_LVDIN_/_RPB9_/_RB9), U1.2 (G1)
unnamed: IC1.4 (~MCLR), J1.5, R2.2

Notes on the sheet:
SCK
3V3
SS2
GND
MCU -> Jetson
SDO2
SDI2
SCK2
SS1
Left
To SNAP
Right
SDI1
SCK1

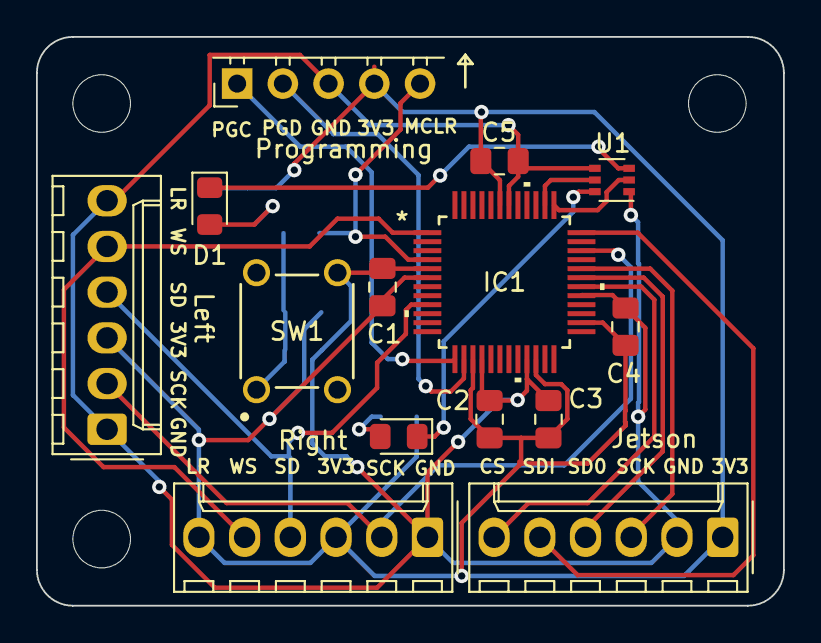
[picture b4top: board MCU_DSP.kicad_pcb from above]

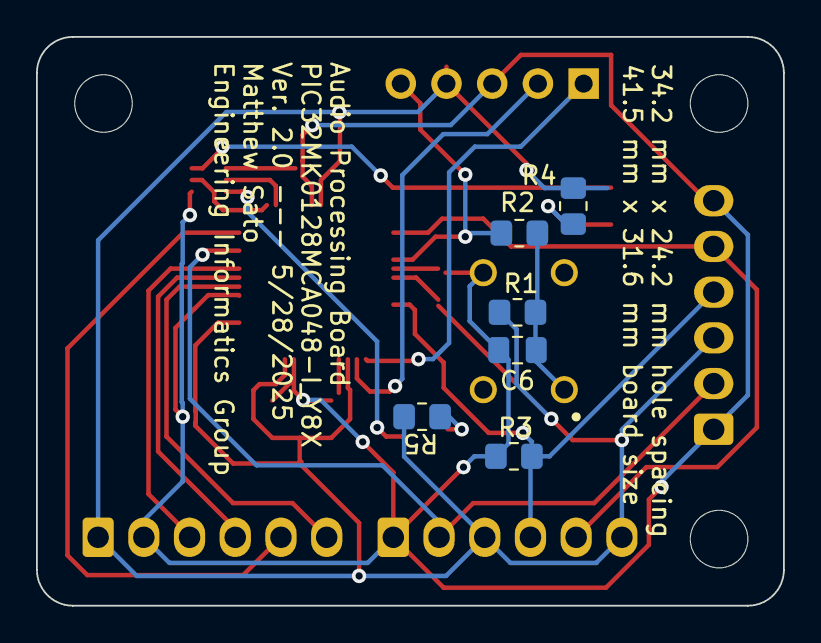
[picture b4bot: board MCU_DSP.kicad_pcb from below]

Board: 2 copper layers, 41.5 x 31.6 mm, 23 parts (6 on the bottom side), 19 nets.
